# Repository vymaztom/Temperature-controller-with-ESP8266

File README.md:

# Regulátor teploty s ESP8266

### Zadání Práce
Prostudujte problematiku elektronického měření teploty. Navrhněte a vyrobte elektronický regulátor teploty s ESP8266. Ten bude spínáním externího topení udržovat teplotu ve stanoveném intervalu. Uvažujte rozsah teplot alespoň -20 až 50 stupňů Celsia. Zařízení bude napájené z externího zdroje. Regulátor se bude konfigurovat prostřednictvím webového rozhraní, kde bude také vidět průběh teplot a stav sepnutí externího topení. Naměřená data budou také odesílána na cloudovou službu pro IoT analýzu dat typu ThingSpeak apod. V rámci semestrálního projektu prostudujte problematiku elektronického měření teploty. Navrhněte schéma a navrhněte a vyrobte desku plošných spojů regulátoru teploty.

### Rozdělení projektu na dílčí části
* prostudování problematiky výber komponet
* výběr vhodného teplotního čidla
* rozbor cloudové služby pro IoT
* návrh DPS (prototyp)
* napsání frimwaru
* návrh finální DPS výroba
* Sepsání dokumentace/práce   

### Realizace projektu

Pro projekt jsem se rozhodl použít ESP8266 a to v provedení ESP-12F. Jedná se o malou destičku, na které je osazen IC ESP8266EX (od něho je odvozen výsledný název) a EEPROM pamět (Flash). Na destičce dále nalezneme několik rezistorů, kondenzátorů, cívek a jeden krystal který taktuje celý obvod. viz schéma zapojení destiky. Za povšimnutí také stojí anténa pro pásmo 2.4GHz, která je realizovaná na DPS a je dopněma LC filtrem typu horní propust (C6, L1, L2).

#### Schéma destičky ESP-XX

Na obrázku můžme vidět pomocí kterých pinů (SPI sběrnice) je k IC připojena Flash pamět, která u mnou zvolené destičky má velikost 4MB.

#### Parametry IC ESP8266EX

* **CPU:** Tensilica L106 32-bit processor
* **I/O rozhraní:** UART/SDIO/SPI/I2C/I2S/IR Remote Contro GPIO/ADC/PWM/LED Light & Button
* **Napájecí napětí:** 2,5 – 3,6V
* **Odběr proudu: průměrně:** 80mA
* **Teplotní rozsah:** -40 – 125°C
* **Pouzdro:** QFN32-pin (5 mm x 5 mm)

*!Na obrázku můžete vidět ESP-12E to se od ESP-12F liší pouze tvarem antény*

#### ESP266 Boot Options

| **GPIO15**<br>**(MTDO)** | **GPIO0** | **GPIO2** | **Mode** | **Comment** |
| :-: | :-: | :-: | :-: | :-: |
| **L** | **H** | **H** | Flash | Boot form SPI Flash |
| **L** | **L** | **H** | UART  | Programing by UART  |
| **H** | **X** | **X** | SDIO  | Boot form SD-card   |

#### Výběr vhodného teplotního čidla

##### Rozbor problematiky

Teplota je jednou ze základních veličin SI soustavy, její jednotka je [K]. V našich končinách se spíše setkáme s jednoutkou stpeň Celsia [°C], která je odvozena od trojného bodu vody. Přepočet mezi těmito jednotkami je velice snadný:

Teplotní čidlo slouží k eletrickému měření teploty, jeho hlavním úkolem je převod okolní teploty na nějakou elektrickou veličinu (odpor, poud, napětí). Čidla můžeme dělit podle mnoha faktorů asi nejzásadnější z nich je jestli je čidlo dotykové nebo ne. V naší aplikaci by bezdotykoké čidlo nemělo smysl, stejně tak by nemělo smysl se tu zaobýrat čidly, které nejsou elektrická, proto se dále zaměřím pouze na dělení dotykových elektrických čidel.  

##### Eleketrická dotykové čidla:

* Odporová kovová
* Odporová polovodičová
* Termoelektrická
* Polovodičová s NP přechodem

##### Citace

* http://skriptum.wz.cz/autom/teplota.htm

#### IoT cloudové sluby

* https://thingspeak.com/
* https://tmep.cz/
* https://iotguru.live/
* https://login.arduino.cc/
* https://www.openhab.org/
* https://aws.amazon.com/free/
* https://cloud.ibm.com/login
* https://cloud.google.com/iot-core
* https://www.fogwing.io/
* https://www.axonize.com/platform/
* https://blynk.io/
* https://www.torryharris.com/products/iot-glue-integration-platform
* https://www.datadoghq.com/product/
* https://www.ixon.cloud/iiot-platform
* https://www.bevywise.com/iot-platform/

##### Citace

* LinuxDays - 3.10.2020 - IoT domov aneb pozvěte si zloděje domů (Petr Šrámek)
* LinuxDays - 3.10.2020 - PiHome - automatizace domácnosti s OpenHAB běžící na Raspberry Pi & Arduino (Michal Novotný)
* LinuxDays - 10.10.2015 - MQTT, protokol pro IoT (Adam Hořčica)

#### CITACE 2

[a1] https://dspace.vutbr.cz/bitstream/handle/11012/17665/final-thesis.pdf?sequence=6
[a2] http://remaxcz.com/old/katalog/snimace/teplota/kl/char/Pt100.pdf
[a4] 
[a5] http://www.ferity.cz/termistory/negohm.pdf
[a6]https://vyvoj.hw.cz/teorie-a-praxe/dokumentace/mereni-teploty-polovodicove-odporove-senzory-teploty.html
[a7] https://cdn.sparkfun.com/datasheets/Sensors/Temp/DS18B20.pdf
[a8] http://robotchip.ru/download/datasheet/AM2302-Datasheet.pdf
[a9] Měření teploty termočlánky. Www.vutbr.cz [online]. [cit. 2017-05-07]. Dostupné z: https://www.vutbr.cz/www_base/zav_prace_soubor_verejne.php?file_id=53351
[a10] https://www.vutbr.cz/www_base/zav_prace_soubor_verejne.php?file_id=149118
[a11] 
[a12] https://thingspeak.com/pages/license_faq
[a13] Portál TMEP.cz: Mapa čidel [online]. [cit. 2020-12-06]. Dostupné z: https://tmep.cz/mapa/
[a14] https://www.myopenhab.org/
[a15] https://www.iso.org/standard/69466.html
[a16] https://blogs.mathworks.com/loren/2016/03/23/explore-your-iot-data-with-thingspeak-and-matlab/
[a17] https://escapequotes.net/esp8266-wemos-d1-mini-pins-and-diagram/
[a18] https://jlcpcb.com/
[a19] https://www.kondik.cz/olovnata-a-bezolovnata-pajka

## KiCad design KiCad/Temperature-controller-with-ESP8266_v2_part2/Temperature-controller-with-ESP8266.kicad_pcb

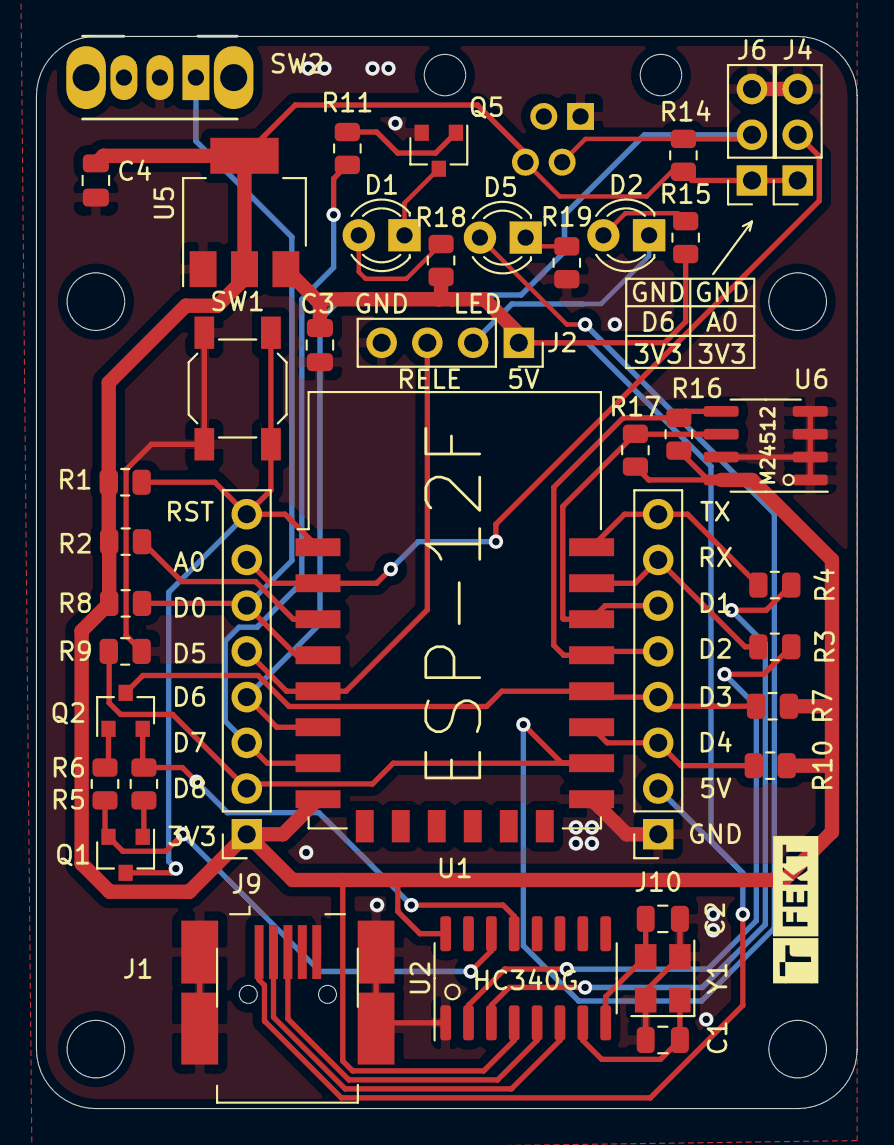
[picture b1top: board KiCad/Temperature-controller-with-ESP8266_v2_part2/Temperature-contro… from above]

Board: 2 copper layers, 45.6 x 59.6 mm, 45 parts (1 on the bottom side), 33 nets.

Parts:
C1, C2: 10p; C_0805_2012Metric
C3, C4: 100n; C_0805_2012Metric
D1, D2, D5: LED; LED_D3.0mm
H1, H2, H3, H4: MountingHole; MountingHole_3.2mm_M3
J1: USB_B_Micro; USB_Micro-B_Molex-67503-1020
J2: Conn_01x04_Male; PinSocket_1x04_P2.54mm_Vertical
J4, J6: Conn_01x03_Male; PinSocket_1x03_P2.54mm_Vertical
J5: RJ13; RJ14_Connfly_DS1133-S4_Horizontal
J9, J10: Conn_01x08_Male; PinSocket_1x08_P2.54mm_Vertical
Q1, Q2, Q5: SS8050-H; SOT-23
R1, R2, R7, R9, R10, R16, R17: 10k; R_0805_2012Metric
R3, R4: 470; R_0805_2012Metric
R5, R6, R11: 1k; R_0805_2012Metric
R8: R; R_0805_2012Metric
R14: 4k7; R_0805_2012Metric
R15: 150; R_0805_2012Metric
R18: 500; R_0805_2012Metric
R19: 200; R_0805_2012Metric
SW1: SW_Push; SW_SPST_SKQG_WithoutStem
SW2: SW_Push_SPDT; SW_CuK_OS102011MA1QN1_SPDT_Angled
U1: ESP-12F; ESP-12E
U2: CH340G; SOIC-16_3.9x9.9mm_P1.27mm
U5: AMS1117-3.3; SOT-223-3_TabPin2
U6: M24512-EEPROM; SOIC-8_3.9x4.9mm_P1.27mm
Y1: Crystal_GND24; Crystal_SMD_SeikoEpson_FA238V-4Pin_3.2x2.5mm

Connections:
+3V3: C4.1, J4.1, J5.4, J6.1, J9.1, R1.2, R2.1, R7.2, R8.1, R10.2, R14.1, R16.1, R17.1, U1.8, U2.4, U2.16, U5.2, U6.8
+5V: C3.1, J1.1, J2.1, J10.2, R15.1, R18.1, U5.3
ADC: J4.2, J9.7, U1.2
BUTTON: J9.6, R8.2, SW2.1, U1.4
DATA: J5.2, J6.2, J9.4, R14.2, U1.6
DTR: Q2.2, R5.2, U2.13
GND: C1.2, C2.2, C3.2, C4.2, J1.5, J1.6, J2.4, J4.3, J5.1, J6.3, J10.1, Q5.2, R9.2, R19.2, SW1.1, SW2.2, U1.15, U2.1, U5.1, U6.1, U6.2, U6.3, U6.4, U6.7, Y1.2, Y1.4
GPIO0: J10.4, Q2.3, R7.1, U1.18
GPIO1: J10.8, R4.2, U1.22
GPIO2: J10.3, R10.1, U1.17
GPIO3: J10.7, R3.1, U1.21
GPIO4: J10.5, R16.2, U1.19, U6.5
GPIO5: J10.6, R17.2, U1.20, U6.6
GPIO13: J9.3, R11.2, U1.7
GPIO14: J2.3, J9.5, U1.5
GPIO15: D5.2, J9.2, R9.1, U1.16
unnamed: C1.1, U2.7, Y1.1
unnamed: C2.1, U2.8, Y1.3
unnamed: D1.1, Q5.3
unnamed: D1.2, R18.2
unnamed: D2.2, R15.2
unnamed: D5.1, R19.1
unnamed: J1.2, U2.6
unnamed: J1.3, U2.5
unnamed: Q1.1, R5.1
unnamed: Q2.1, R6.1
unnamed: Q5.1, R11.1
unnamed: R2.2, U1.3
unnamed: R3.2, U2.2
unnamed: R4.1, U2.3
RELE_D: D2.1, J2.2
RST: J9.8, Q1.3, R1.1, SW1.2, U1.1
RTS: Q1.2, R6.2, U2.14

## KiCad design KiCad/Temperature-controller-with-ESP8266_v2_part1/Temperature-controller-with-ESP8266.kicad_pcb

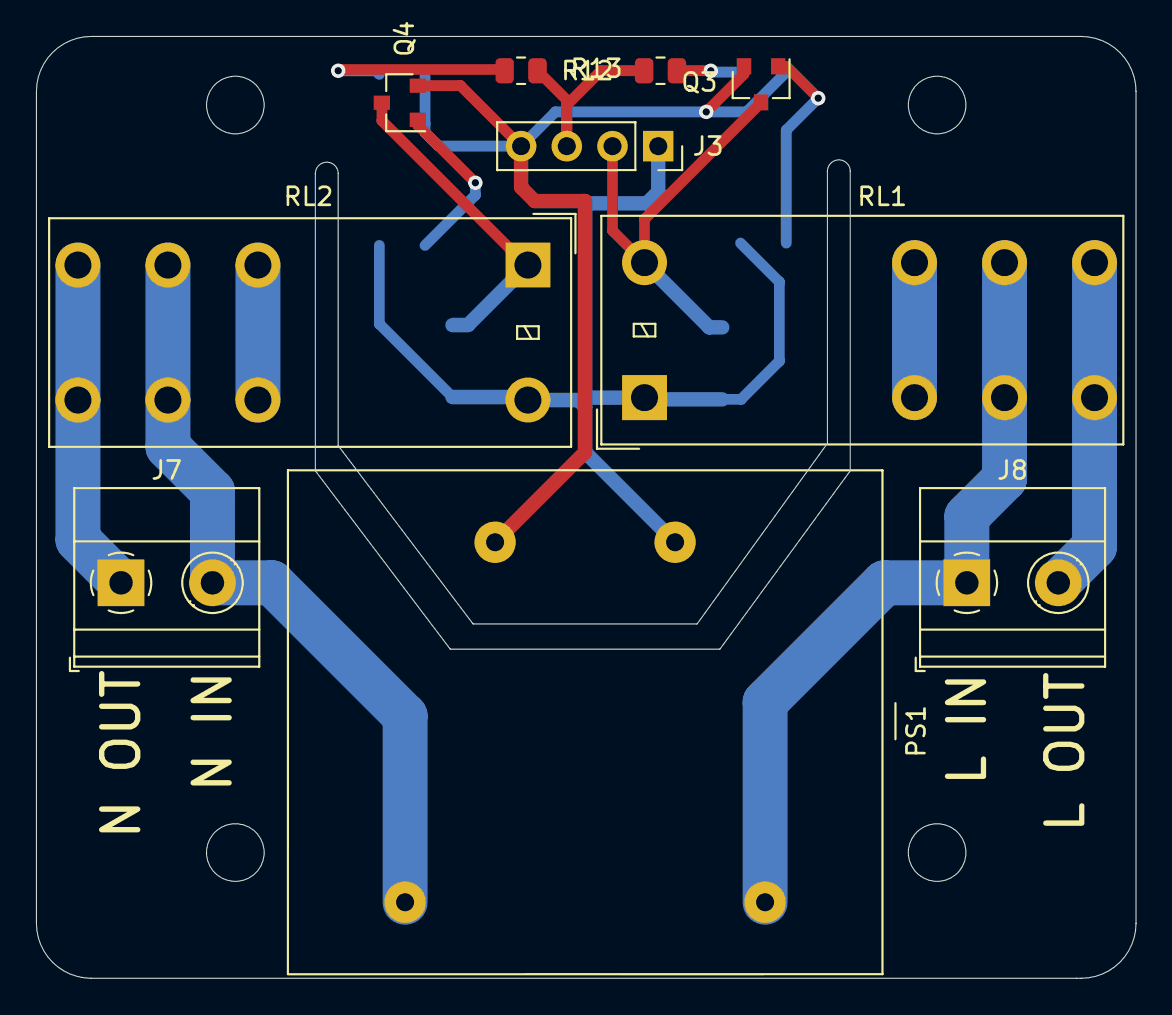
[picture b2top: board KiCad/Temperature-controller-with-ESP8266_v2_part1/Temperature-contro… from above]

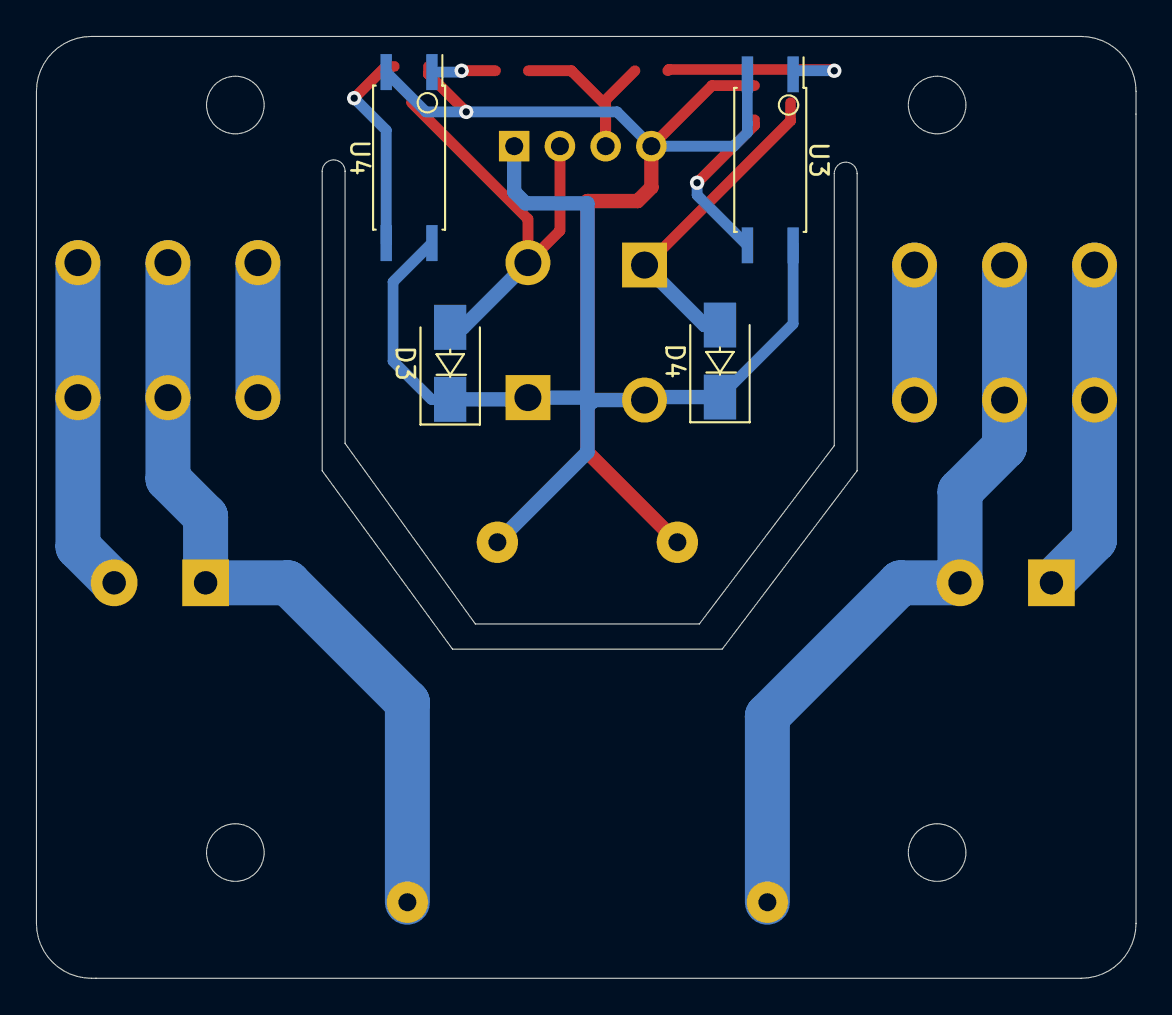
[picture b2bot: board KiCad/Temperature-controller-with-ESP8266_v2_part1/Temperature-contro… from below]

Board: 2 copper layers, 61.1 x 52.3 mm, 18 parts (4 on the bottom side), 15 nets.

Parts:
D3, D4: D; D_SMA
H5, H6, H7, H8: MountingHole; MountingHole_3.2mm_M3
J3: Conn_01x04_Female; PinSocket_1x04_P2.54mm_Vertical
J7, J8: Screw_Terminal_01x02; TerminalBlock_Phoenix_MKDS-1,5-2-5.08_1x02_P5.08mm_Horizont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
PS1: Converter_ACDC_MYRRA_47162
Q3, Q4: MMBT5551L; SOT-23
R12, R13: 1k; R_0805_2012Metric
RL1, RL2: G2RL-2-DC5; Relay_DPDT_Omron_G2RL
U3, U4: EL817; SO-4_7.6x3.6mm_P2.54mm

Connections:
+5V: D3.1, D4.1, J3.1, PS1.7, RL1.1, RL2.8, U3.4, U4.4
GND: J3.4, PS1.9, Q3.2, Q4.2, U3.2, U4.2
GPIO14: J3.3, R12.2, R13.2
L: J8.1, PS1.5, RL1.3, RL1.6
L_OUT: J8.2, RL1.4, RL1.5
N: J7.2, PS1.1, RL2.3, RL2.6
N_OUT: J7.1, RL2.4, RL2.5
unnamed: D4.2, Q4.3, RL2.1
unnamed: Q3.1, U4.3
unnamed: Q4.1, U3.3
unnamed: R12.1, U3.1
unnamed: R13.1, U4.1
unnamed: RL1.2, RL1.7
unnamed: RL2.2, RL2.7
RELE_D: D3.2, J3.2, Q3.3, RL1.8

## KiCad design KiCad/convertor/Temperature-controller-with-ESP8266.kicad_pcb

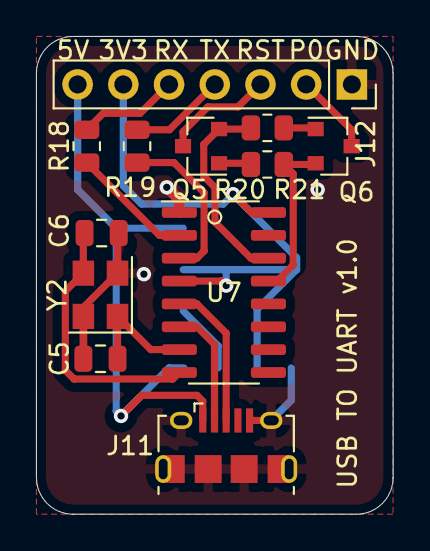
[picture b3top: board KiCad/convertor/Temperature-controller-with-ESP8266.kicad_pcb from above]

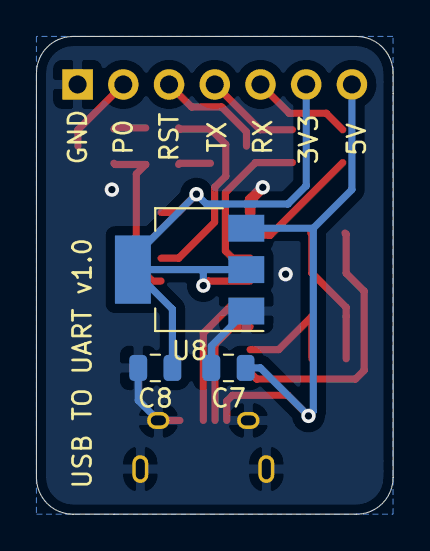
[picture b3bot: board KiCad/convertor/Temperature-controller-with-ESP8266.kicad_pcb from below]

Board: 2 copper layers, 19.8 x 26.5 mm, 15 parts (3 on the bottom side), 17 nets.

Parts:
C5, C6: 10p; C_0805_2012Metric
C7, C8: 100n; C_0805_2012Metric
J11: USB_B_Micro; USB_Micro-B_Amphenol_10118194_Horizontal
J12: Conn_01x07_Male; PinSocket_1x07_P2.54mm_Vertical
Q5, Q6: SS8050-H; SOT-23
R18, R19: 470; R_0805_2012Metric
R20, R21: 1k; R_0805_2012Metric
U7: CH340G; SOIC-16_3.9x9.9mm_P1.27mm
U8: AMS1117-3.3; SOT-223-3_TabPin2
Y2: Crystal_GND24; Crystal_SMD_SeikoEpson_FA238V-4Pin_3.2x2.5mm

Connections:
DTR1: Q6.2, R20.2, U7.13
unnamed: C5.1, U7.7, Y2.1
unnamed: C5.2, C6.2, C7.2, C8.2, J11.5, J11.6, J12.1, U7.1, U8.1, Y2.2, Y2.4
unnamed: C6.1, U7.8, Y2.3
unnamed: C7.1, J11.1, J12.7, U8.3
unnamed: C8.1, J12.6, U7.4, U7.16, U8.2
unnamed: J11.2, U7.6
unnamed: J11.3, U7.5
unnamed: J12.2, Q6.3
unnamed: J12.3, Q5.3
unnamed: J12.4, R19.2
unnamed: J12.5, R18.1
unnamed: Q5.1, R20.1
unnamed: Q6.1, R21.1
unnamed: R18.2, U7.2
unnamed: R19.1, U7.3
RTS1: Q5.2, R21.2, U7.14

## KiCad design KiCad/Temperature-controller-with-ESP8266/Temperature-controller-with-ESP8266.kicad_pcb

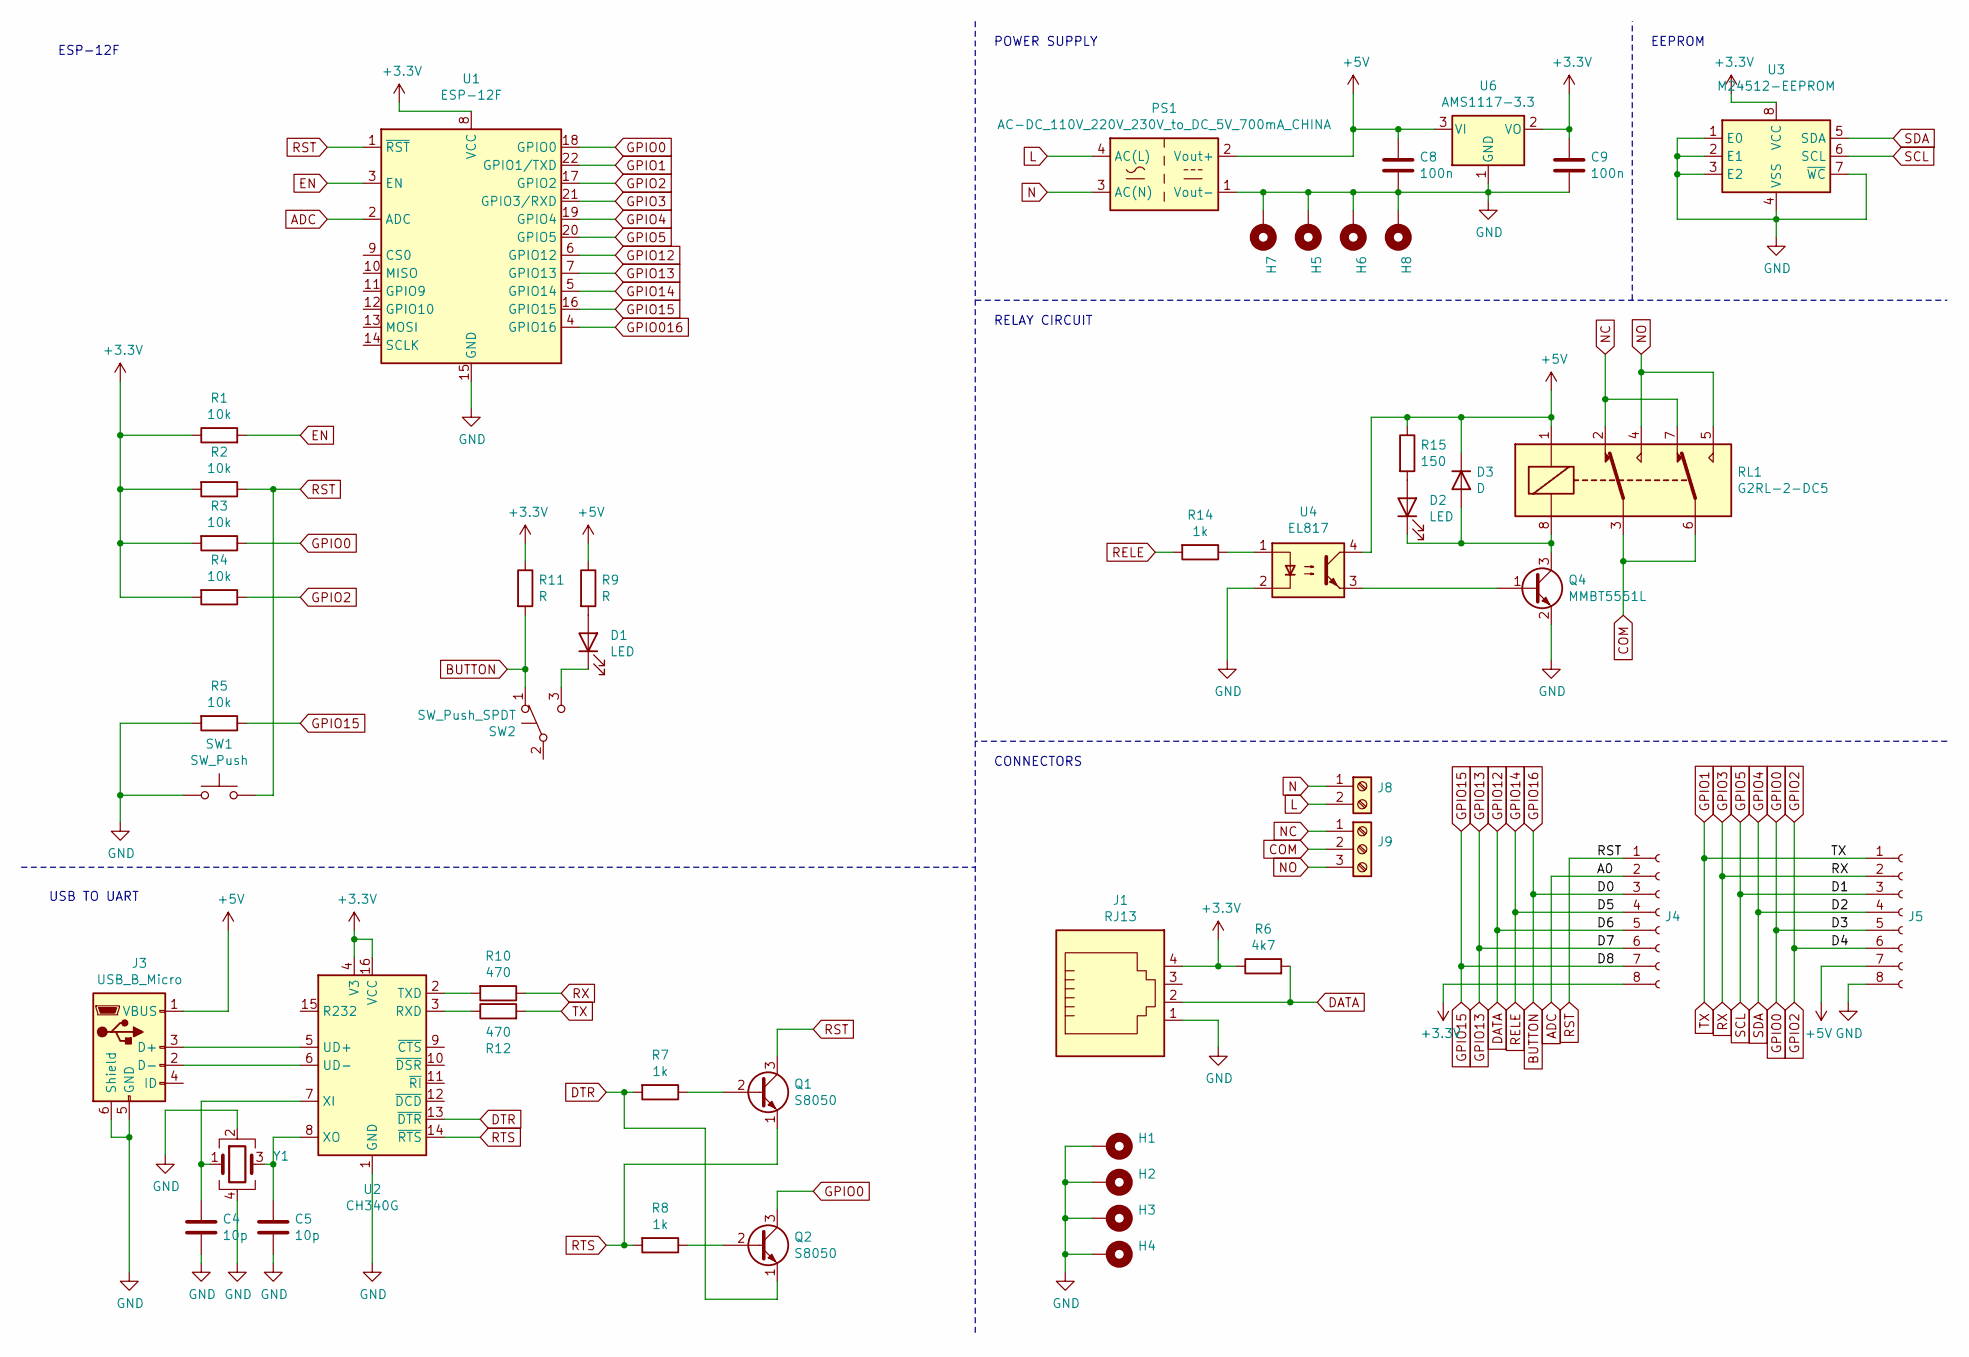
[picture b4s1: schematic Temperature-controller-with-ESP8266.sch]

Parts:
C4, C5: 10p; C_0805_2012Metric
C8, C9: 100n; C_0805_2012Metric
D1, D2: LED; LED_D3.0mm
D3: D; D_SMA
H1, H2, H3, H4: MountingHole_Pad; MountingHole_3.2mm_M3_Pad_Via
H5, H6, H7, H8: MountingHole_Pad; PinHeader_1x01_P2.00mm_Vertical
J1: RJ13; RJ14_Connfly_DS1133-S4_Horizontal
J3: USB_B_Micro; USB_Micro-B_Molex-67503-1020
J4, J5: Conn_01x08_Female; PinSocket_1x08_P2.54mm_Vertical
J8: Screw_Terminal_01x02; TerminalBlock_Phoenix_MKDS-1,5-2-5.08_1x02_P5.08mm_Horizont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
J9: Screw_Terminal_01x03; TerminalBlock_Phoenix_MKDS-1,5-3-5.08_1x03_P5.08mm_Horizont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
PS1: AC-DC_110V_220V_230V_to_DC_5V_700mA_CHINA
Q1, Q2: S8050; SOT-23
Q4: MMBT5551L; SOT-23
R1, R2, R3, R4, R5: 10k; R_0805_2012Metric
R6: 4k7; R_0805_2012Metric
R7, R8, R14: 1k; R_0805_2012Metric
R9, R11: R; R_0805_2012Metric
R10, R12: 470; R_0805_2012Metric
R15: 150; R_0805_2012Metric
RL1: G2RL-2-DC5; Relay_DPDT_Omron_G2RL
SW1: SW_Push; SW_SPST_SKQG_WithoutStem
SW2: SW_Push_SPDT; SW_CuK_OS102011MA1QN1_SPDT_Angled
U1: ESP-12F; ESP-12E
U2: CH340G; SOIC-16_3.9x9.9mm_P1.27mm
U3: M24512-EEPROM; SOIC-8_3.9x4.9mm_P1.27mm
U4: EL817; SO-4_7.6x3.6mm_P2.54mm
U6: AMS1117-3.3; SOT-223-3_TabPin2
Y1: Crystal_GND24; Crystal_SMD_SeikoEpson_FA238V-4Pin_3.2x2.5mm

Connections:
+3V3: C9.1, J1.4, J4.8, R1.1, R2.2, R3.2, R4.2, R6.1, R11.1, U1.8 (VCC), U2.4 (V3), U2.16 (VCC), U3.8 (VCC), U6.2 (VO)
+5V: C8.1, D3.1 (K), J3.1 (VBUS), J5.7, PS1.2 (Vout+), R9.1, R15.1, RL1.1, U4.4, U6.3 (VI)
ADC: J4.2, U1.2 (ADC)
BUTTON: J4.3, R11.2, SW2.1 (A)
COM: J9.2, RL1.3, RL1.6
DATA: J1.2, J4.5, R6.2, U1.6 (GPIO12)
DTR: Q2.1 (E), R7.2, U2.13 (~DTR)
EN: R1.2, U1.3 (EN)
GND: C4.2, C5.2, C8.2, C9.2, H1.1, H2.1, H3.1, H4.1, H5.1, H6.1, H7.1, H8.1, J1.1, J3.5 (GND), J3.6 (Shield), J5.8, PS1.1 (Vout-), Q4.2 (E), R5.2, SW1.1, SW2.2 (B), U1.15 (GND), U2.1 (GND), U3.1 (E0), U3.2 (E1), U3.3 (E2), U3.4 (VSS), U3.7 (~WC), U4.2, U6.1 (GND), Y1.2, Y1.4
GPIO0: J5.5, Q2.3 (C), R3.1, U1.18 (GPIO0)
GPIO1: J5.1, R12.2, U1.22 (GPIO1/TXD)
GPIO2: J5.6, R4.1, U1.17 (GPIO2)
GPIO3: J5.2, R10.1, U1.21 (GPIO3/RXD)
GPIO4: J5.4, U1.19 (GPIO4), U3.5 (SDA)
GPIO5: J5.3, U1.20 (GPIO5), U3.6 (SCL)
GPIO13: J4.6, U1.7 (GPIO13)
GPIO14: J4.4, R14.2, U1.5 (GPIO14)
GPIO15: J4.7, R5.1, U1.16 (GPIO15)
L: J8.2, PS1.4 (AC(L))
N: J8.1, PS1.3 (AC(N))
NC: J9.1, RL1.2, RL1.7
NO: J9.3, RL1.4, RL1.5
unnamed: C4.1, U2.7 (XI), Y1.1
unnamed: C5.1, U2.8 (XO), Y1.3
unnamed: D1.1 (K), SW2.3 (C)
unnamed: D1.2 (A), R9.2
unnamed: D2.1 (K), D3.2 (A), Q4.3 (C), RL1.8
unnamed: D2.2 (A), R15.2
unnamed: J3.2 (D-), U2.6 (UD-)
unnamed: J3.3 (D+), U2.5 (UD+)
unnamed: Q1.2 (B), R7.1
unnamed: Q2.2 (B), R8.1
unnamed: Q4.1 (B), U4.3
unnamed: R10.2, U2.2 (TXD)
unnamed: R12.1, U2.3 (RXD)
unnamed: R14.1, U4.1
RST: J4.1, Q1.3 (C), R2.1, SW1.2, U1.1 (~RST)
RTS: Q1.1 (E), R8.2, U2.14 (~RTS)

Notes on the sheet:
RELAY CIRCUIT
CONNECTORS
USB TO UART
POWER SUPPLY
ESP-12F
EEPROM

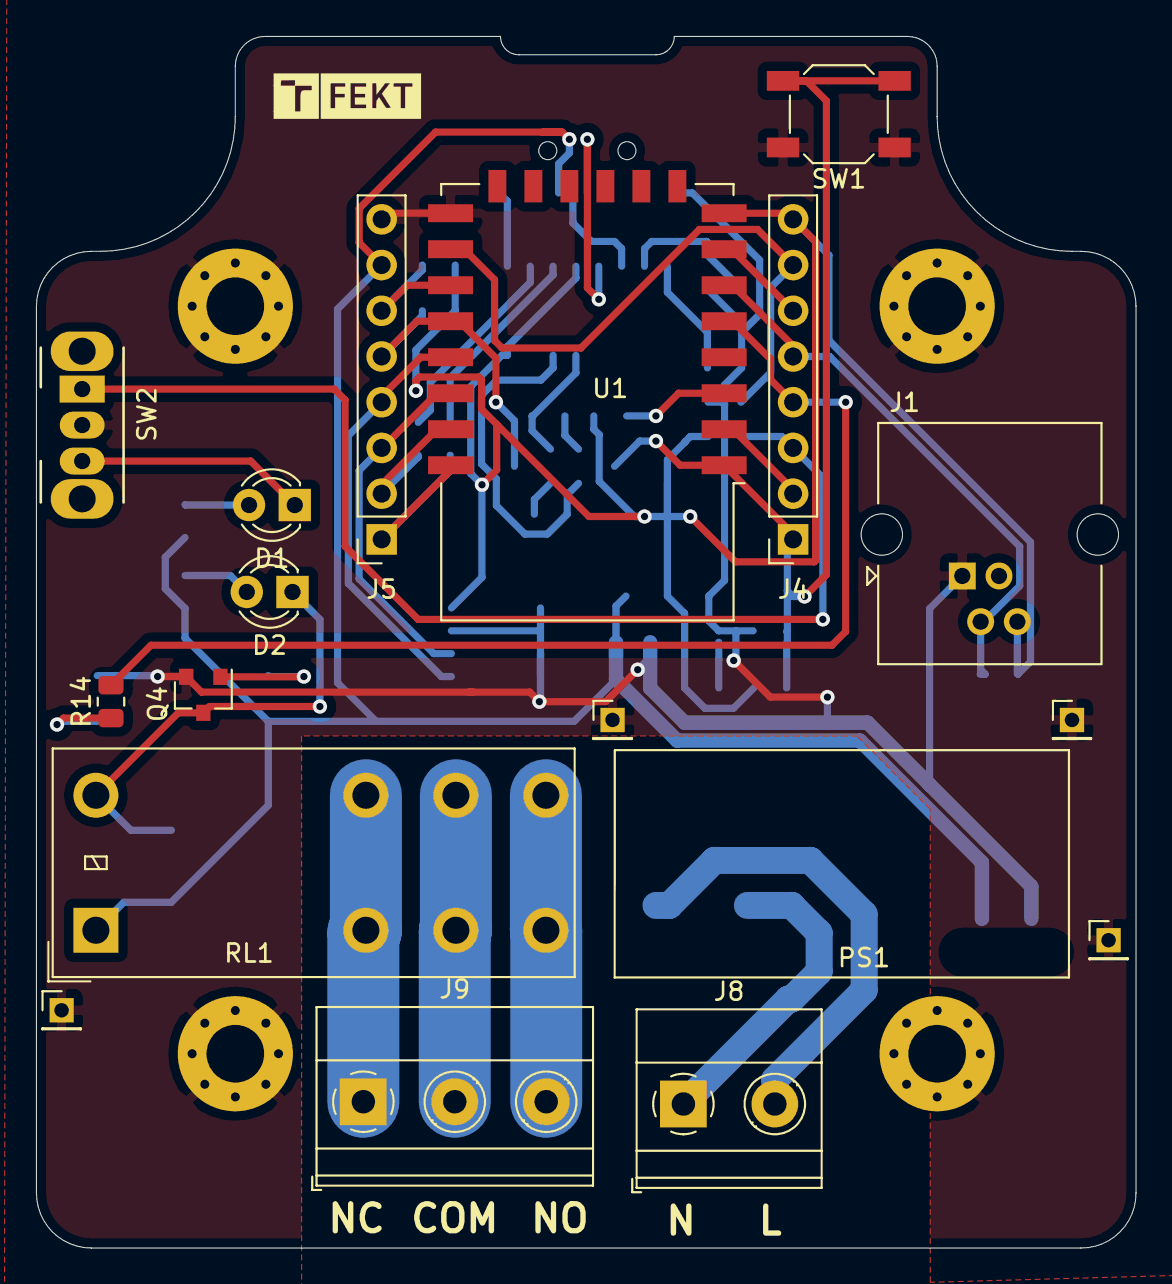
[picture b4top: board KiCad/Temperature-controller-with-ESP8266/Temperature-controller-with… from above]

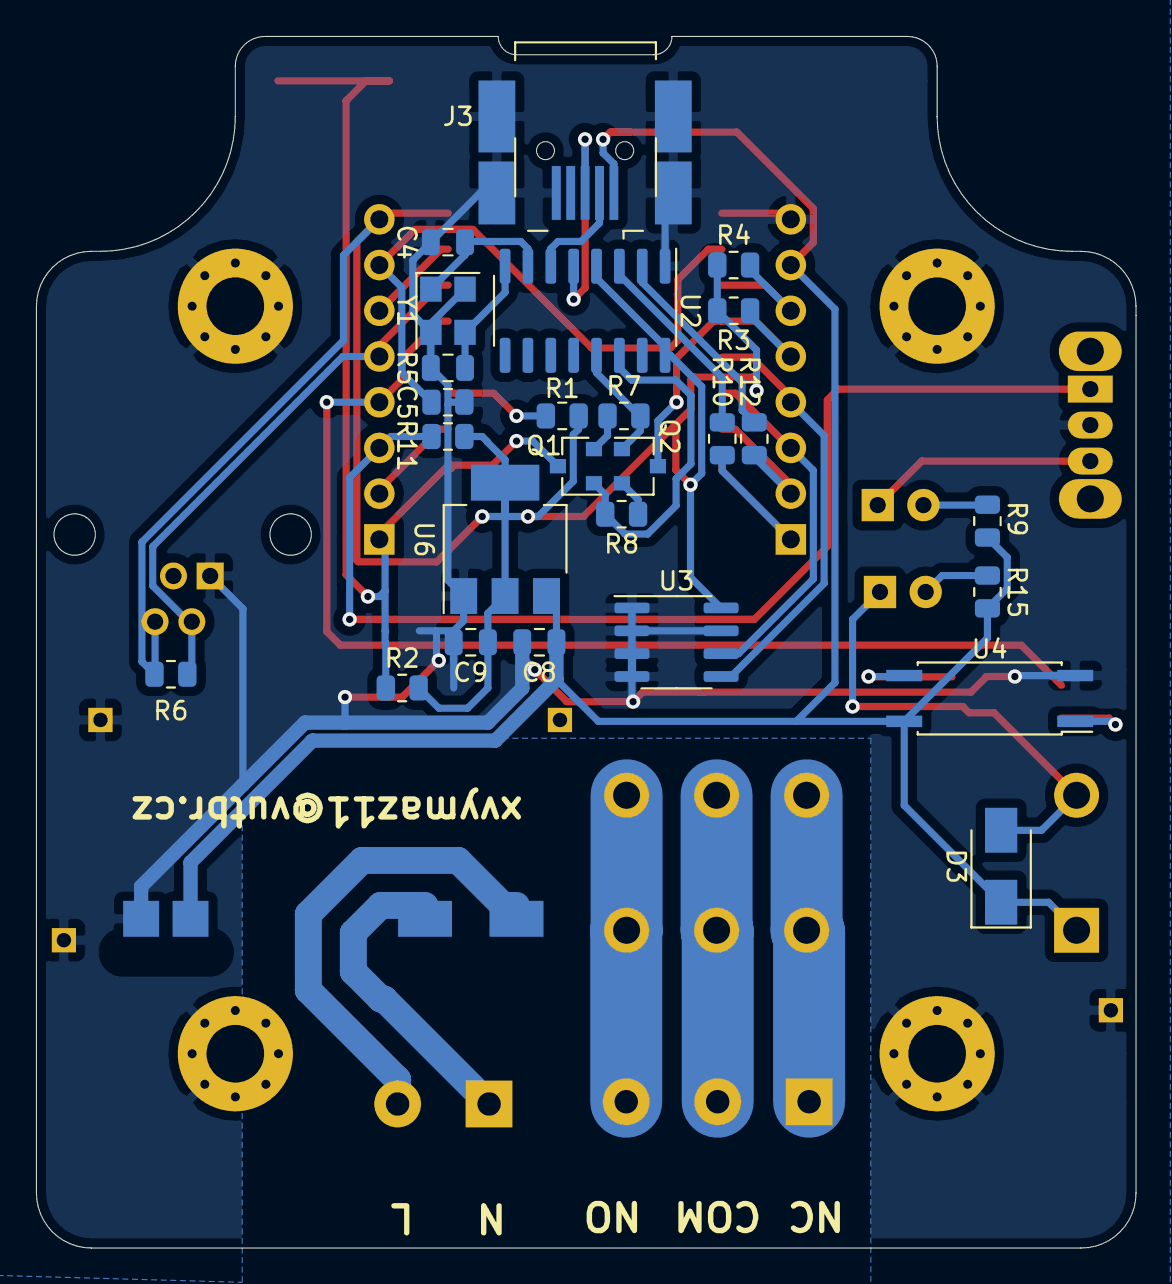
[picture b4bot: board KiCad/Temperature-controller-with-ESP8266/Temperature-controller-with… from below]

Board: 2 copper layers, 61.1 x 67.3 mm, 48 parts (26 on the bottom side), 38 nets.

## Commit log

2020-09-29 přídáno zadání projektu
2020-10-05 Edited README.md add pictures
2020-10-08 add article of temperature sensors
2020-10-11 migration files into ubuntu desktop
2020-10-17 add temperature sensors data
2020-10-21 Konzultace
2020-10-21 add boot table
2020-11-22 Add Obr from osciloskop
2020-11-22 Add photos of workable desk
2020-11-24 add screan from osciloskope
2020-12-07 citace add
2020-12-11 zaloha
2021-03-23 zaloha 23.03.21
2021-03-27 zaloha-27.03.2021
2021-05-17 Test of Git+ module atom
2021-05-18 added wifi nets list
2021-05-22 Zaloha 23.05.2021
